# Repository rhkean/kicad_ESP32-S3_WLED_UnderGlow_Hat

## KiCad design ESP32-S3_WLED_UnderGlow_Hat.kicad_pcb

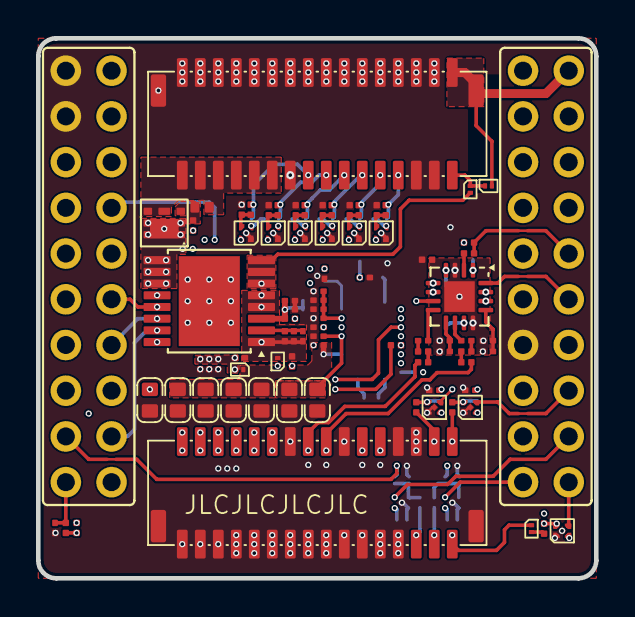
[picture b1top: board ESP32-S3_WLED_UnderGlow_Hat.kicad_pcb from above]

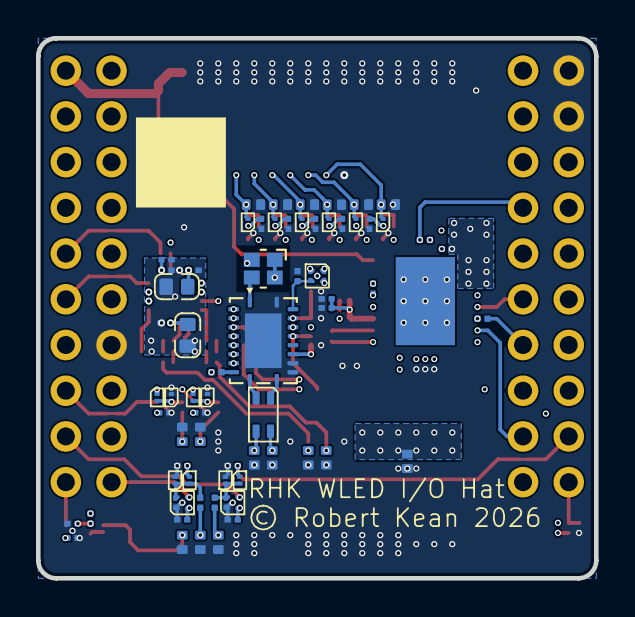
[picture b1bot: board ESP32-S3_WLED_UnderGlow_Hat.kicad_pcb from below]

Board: 6 copper layers, 31.0 x 30.0 mm, 149 parts (66 on the bottom side), 85 nets.

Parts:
C301, C702, C703, C705, C711, C713, C714, C715, C716, C717, C801, C802, C803, C804, C805, C806, C807, C808, C809, C810, C812, C813, C815, C819, C820, C821, C822, C901, C902, C903, C904, C905, C906, C907, C908, C909, C911, C912, C913, C914, C916: 0.1uF; C_0201_Dense
C701, C704, C706, C707, C708, C709, C710, C811, C816: 22uF; C_0603_Dense
C814, C817, C818: 1uF; C_0201_Dense
C910, C915: 4.7nF; C_0201_Dense
CMC701: CMC 0805; CMC_0805
CN301, CN302: SM32B-NSHDZS-1-TF; JST_NSHD_SM32B-NSHD_2x16_P1.0mm_Horizontal_SMD
D701, D801, D803, D804, D806, D807, D809, D810, D812, D813, D901, D902, D903, D904, D908, D909, D912, D913, D914: PMEG4002ESFYL; DFN0603-2
D702, D703, D815, D816: SZESD7241N2T5G; DFN1006-2
D704, D802, D805, D808, D811, D814, D905, D906, D907, D910, D911, D915, D916: D15V0H1U2LP-7B; DFN1006-2
Q901: NTLJS17D0P03P8Z; WDFN6-4_2.05x2.05mm_P0.65mm
R301, R302, R701, R704, R805, R811, R904, R905, R907, R908, R912, R913, R914, R917, R918: 5k1; R_0201_Dense
R702, R807, R808, R809, R810, R812, R901, R902, R903, R906, R910, R911, R915, R916: 33R; R_0201_Dense
R703, R806: 470R; R_0201_Dense
R801, R802, R803, R804: 26k1; R_0201_Dense
R813: 0R; R_0201_Dense
R909: 100k; R_0201_Dense
U301: ESP32-S3_D1_Pico
U701: TCAN4550-Q1; Texas_RGY_R-PVQFN-N20_EP2.05x3.05mm
U702, U801, U802, U803, U804, U805, U901, U902, U904, U905, U906, U907: 74LV1T125; X2SON5_SOT1226_0.8x0.8mm
U806: ES7241D; QFN-16-1EP_3x3mm_P0.5mm_EP1.7x1.7mm
U903: TPS2HCS10A-Q1; Texas_HTSSOP-16-1EP_5.0x4.4mm_P0.65mm_EP5.0x3.4mm_Mask3.313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
Y701: 40MHz; Oscillator_SMD_Abracon_ASAAIG-4Pin_2.0x1.6mm

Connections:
+3V3: C701.1, C702.1, C711.1, C717.1, C801.1, C802.1, C803.1, C804.1, C805.1, C811.1, C812.1, C813.1, C814.1, C815.1, C816.1, R301.2, R701.2, R811.2, R901.1, U301.8 (+3V3_{out}), U301.18 (+3V3), U701.17 (V_{IO}), U702.2 (A), U702.5 (VCC), U801.5 (VCC), U802.5 (VCC), U803.5 (VCC), U804.5 (VCC), U805.5 (VCC), U806.1 (V_{DD}P), U806.4 (V_{DD}D), U806.11 (V_{DD}A), U806.14 (M1), U806.15 (M0), Y701.1 (EN), Y701.4 (Vdd)
+5V_{FUSED}: C806.1, C807.1, C808.1, C809.1, C901.1, C902.1, C903.1, C904.1, C905.1, D801.1 (K), D804.1 (K), D807.1 (K), D810.1 (K), D902.1 (K), D903.1 (K), D908.1 (K), D909.1 (K), D913.1 (K), D914.1 (K), R805.2, U301.9 (+5V_{FUSED_{out}}), U901.5 (VCC), U902.5 (VCC), U904.5 (VCC), U905.5 (VCC), U906.5 (VCC), U907.5 (VCC)
+V_{BAT}: C907.1, C908.1, C909.1, C910.1, CN302.1, CN302.3, CN302.5, CN302.7, CN302.9, CN302.11, D701.2 (A), D704.1 (K), U903.EP (V_{BB})
+V_{SW}: CN301.21, CN301.23, CN301.25 (Pin_23), CN301.27 (Pin_23), CN301.29 (Pin_23), CN301.31 (Pin_23), D907.1 (K), Q901.3 (S), Q901.4 (S)
/IO_Board/AUX_{L}: CN302.15, D815.1 (A1), R807.2
/IO_Board/AUX_{R}: CN302.17, D816.1 (A1), R810.2
/IO_Board/Brake: U301.39 (IO16), U802.4 (Y)
/IO_Board/Brake_{IN}: CN302.28 (Pin_24), D805.1 (K), R802.2
/IO_Board/CAN Bus/+V_{SUP}: C705.1, C707.1, C708.1, C709.1, C710.1, D701.1 (K), U701.14 (V_{SUP})
/IO_Board/CAN Bus/CAN_F_N: CMC701.2, U701.10 (CANL)
/IO_Board/CAN Bus/CAN_F_P: CMC701.1, U701.11 (CANH)
/IO_Board/CAN Bus/FLTR: C713.1, C714.1, C715.1, C716.1, U701.18 (FLTR)
/IO_Board/CAN Bus/GPO2: R703.2, U701.9 (GPO2)
/IO_Board/CAN Bus/OSC1: U701.1 (OSC1), Y701.3 (OUT)
/IO_Board/CAN Bus/RST: R704.2, U701.19 (RST), U702.4 (Y)
/IO_Board/CAN Bus/SDO: R702.1, U701.6 (SDO)
/IO_Board/CAN Bus/V_{CC_{OUT}}: C703.1, C704.1, C706.1, U701.16 (V_{CCOUT})
/IO_Board/CAN_N: CMC701.3, CN302.23, D702.1 (A1)
/IO_Board/CAN_P: CMC701.4, CN302.21, D703.1 (A1)
/IO_Board/Data1: CN301.17, D902.2 (A), D905.1 (K), R902.1
/IO_Board/Data2: CN301.15, D903.2 (A), D906.1 (K), R903.1
/IO_Board/Data3: CN301.13, D908.2 (A), D910.1 (K), R910.1
/IO_Board/Data4: CN301.11, D909.2 (A), D911.1 (K), R911.1
/IO_Board/Data5: CN301.9, D913.2 (A), D915.1 (K), R915.1
/IO_Board/Data6: CN301.7, D914.2 (A), D916.1 (K), R916.1
/IO_Board/FSPI_{CLK}: U301.6 (FSPI_{CLK}), U701.4 (SCLK), U903.16 (SCLK)
/IO_Board/FSPI_{MISO}: R702.2, R906.2, U301.17 (FSPI_{MISO})
/IO_Board/FSPI_{MOSI}: U301.16 (FSPI_{MOSI}), U701.5 (SDI), U903.13 (SDI)
/IO_Board/GR86 Inputs/A_{IN}L: C817.2, U806.8 (A_{IN}L)
/IO_Board/GR86 Inputs/A_{IN}R: C818.2, U806.10 (A_{IN}R)
/IO_Board/GR86 Inputs/Brake_F: D804.2 (A), D806.1 (K), R802.1, U802.2 (A)
/IO_Board/GR86 Inputs/GND3: C811.2, C812.2, C813.2, C814.2, C815.2, C816.2, C819.2, C820.2, C821.2, C822.2, R813.1, U806.3 (GND_{D}), U806.12 (GND_{A}), U806.17 (GND_{P})
/IO_Board/GR86 Inputs/LTurn_F: D810.2 (A), D812.1 (K), R804.1, U804.2 (A)
/IO_Board/GR86 Inputs/RC_{808-817}: C817.1, R808.1
/IO_Board/GR86 Inputs/RC_{809-818}: C818.1, R809.1
/IO_Board/GR86 Inputs/REF_{P}: C819.1, C820.1, U806.13 (REF_{P})
/IO_Board/GR86 Inputs/REF_{Q}: C821.1, C822.1, U806.9 (REF_{Q})
/IO_Board/GR86 Inputs/RR_{807-808}: R807.1, R808.2
/IO_Board/GR86 Inputs/RR_{809-810}: R809.2, R810.1
/IO_Board/GR86 Inputs/RTurn_F: D807.2 (A), D809.1 (K), R803.1, U803.2 (A)
/IO_Board/GR86 Inputs/Rev_F: D801.2 (A), D803.1 (K), R801.1, U801.2 (A)
/IO_Board/GR86 Inputs/SD_{OUT}: R812.2, U806.2 (SD_{OUT})
/IO_Board/GR86 Inputs/~Dome_F: C810.1, R805.1, R806.2, U805.2 (A)
/IO_Board/I^{2}S_{MCLK}: U301.36 (I^{2}S_{MCLK}), U806.16 (MCLK)
/IO_Board/I^{2}S_{SCK}: U301.26 (I^{2}S_{SCK}), U806.5 (SCLK)
/IO_Board/I^{2}S_{SD}: R811.1, R812.1, U301.35 (I^{2}S_{SD})
/IO_Board/I^{2}S_{WS}: U301.37 (I^{2}S_{WS}), U806.6 (LRCK)
/IO_Board/LED1: U301.32 (IO44), U901.2 (A)
/IO_Board/LED2: U301.23 (IO43), U902.2 (A)
/IO_Board/LED3: U301.33 (IO42), U904.2 (A)
/IO_Board/LED4: U301.24 (IO40), U905.2 (A)
/IO_Board/LED5: U301.34 (IO41), U906.2 (A)
/IO_Board/LED6: U301.25 (IO38), U907.2 (A)
/IO_Board/LTurn: U301.29 (IO17), U804.4 (Y)
/IO_Board/LTurn_{IN}: CN302.29 (Pin_23), D811.1 (K), R804.2
/IO_Board/RLY+: CN301.1, D901.1 (K), D904.1 (K)
/IO_Board/RTurn: U301.38 (IO18), U803.4 (Y)
/IO_Board/RTurn_{IN}: CN302.31 (Pin_23), D808.1 (K), R803.2
/IO_Board/Reverse: U301.30 (IO08), U801.4 (Y)
/IO_Board/Reverse_{IN}: CN302.30 (Pin_24), D802.1 (K), R801.2
/IO_Board/WD: U301.13 (IO02), U701.3 (GPIO1)
/IO_Board/WLED Outputs/LED1_{Buf}: R902.2, R904.1, U901.4 (Y)
/IO_Board/WLED Outputs/LED2_{Buf}: R903.2, R905.1, U902.4 (Y)
/IO_Board/WLED Outputs/LED3_{Buf}: R910.2, R912.1, U904.4 (Y)
/IO_Board/WLED Outputs/LED4_{Buf}: R911.2, R913.1, U905.4 (Y)
/IO_Board/WLED Outputs/LED5_{Buf}: R915.2, R917.1, U906.4 (Y)
/IO_Board/WLED Outputs/LED6_{Buf}: R916.2, R918.1, U907.4 (Y)
/IO_Board/WLED Outputs/SDO: R906.1, U903.14 (SDO)
/IO_Board/WLED Outputs/SNS: C915.1, R907.1, R908.1, U903.2 (SNS)
/IO_Board/WLED Outputs/VDD_{HSS}: C911.1, C912.1, C913.1, C914.1, R901.2, U903.3 (V_{DD})
/IO_Board/WLED Outputs/V_{GATE}: D907.2 (A), Q901.2 (G), R909.2
/IO_Board/WLED Outputs/V_{OUT1}: C906.1, D901.2 (A), U903.6 (V_{OUT1}), U903.7 (V_{OUT1}), U903.8 (V_{OUT1})
/IO_Board/WLED Outputs/V_{OUT2}: C916.1, Q901.1 (D), U903.9 (V_{OUT2}), U903.10 (V_{OUT2}), U903.11 (V_{OUT2})
/IO_Board/~CS_{CAN}: U301.20 (I005), U701.7 (~CS)
/IO_Board/~CS_{HSS}: U301.19 (IO06), U903.15 (~CS)
/IO_Board/~Dome_{IN}: CN302.32 (Pin_24), D813.1 (K), D814.1 (K)
/IO_Board/~Dome: U301.40 (IO15), U805.4 (Y)
/IO_Board/~FLT_{BUS}: R301.1, R302.2, U701.8 (~INT), U903.12 (FLT)
/IO_Board/~FLT_{GBL}: C301.1, R302.1, U301.10 (IO07)
/IO_Board/~Reset Node: R703.1, U301.11 (EN/~RST), U702.1 (OE), U806.7 (~Reset)
/IO_Board/~Wake: R701.1, U301.14 (IO04), U701.2 (~WKRQ)
GND: C301.2, C701.2, C702.2, C703.2, C704.2, C705.2, C706.2, C707.2, C708.2, C709.2, C710.2, C711.2, C713.2, C714.2, C715.2, C716.2, C717.2, C801.2, C802.2, C803.2, C804.2, C805.2, C806.2, C807.2, C808.2, C809.2, C810.2, C901.2, C902.2, C903.2, C904.2, C905.2, C907.2, C908.2, C909.2, C911.2, C912.2, C913.2, C914.2, CN301.3, CN301.4, CN301.5, CN301.6, CN301.8, CN301.10, CN301.12, CN301.14, CN301.16, CN301.18, CN301.19, CN301.20, CN301.22, CN301.24, CN301.26 (Pin_24), CN301.28 (Pin_24), CN301.30 (Pin_24), CN301.32 (Pin_24), CN301.MP2 (MountPin), CN302.2, CN302.4, CN302.6, CN302.8, CN302.10, CN302.12, CN302.13, CN302.14, CN302.16, CN302.18, CN302.19, CN302.20, CN302.22, CN302.24, CN302.25 (Pin_23), CN302.26 (Pin_24), CN302.27 (Pin_23), CN302.MP1 (MountPin), CN302.MP2 (MountPin), D702.2 (A2), D703.2 (A2), D704.2 (A), D802.2 (A), D803.2 (A), D805.2 (A), D806.2 (A), D808.2 (A), D809.2 (A), D811.2 (A), D812.2 (A), D814.2 (A), D815.2 (A2), D816.2 (A2), D905.2 (A), D906.2 (A), D910.2 (A), D911.2 (A), D912.1 (K), D915.2 (A), D916.2 (A), R704.1, R813.2, R904.2, R905.2, R912.2, R913.2, R914.2, R917.2, R918.2, U301.1 (GND), U301.2 (GND), U301.27 (GND), U701.12 (WAKE), U701.13 (GND), U701.20 (OSC2), U701.21 (GND), U702.3 (GND), U801.1 (OE), U801.3 (GND), U802.1 (OE), U802.3 (GND), U803.1 (OE), U803.3 (GND), U804.1 (OE), U804.3 (GND), U805.1 (OE), U805.3 (GND), U901.1 (OE), U901.3 (GND), U902.1 (OE), U902.3 (GND), U904.1 (OE), U904.3 (GND), U905.1 (OE), U905.3 (GND), U906.1 (OE), U906.3 (GND), U907.1 (OE), U907.3 (GND), Y701.2 (GND)
GND0: CN301.2, CN301.MP1 (MountPin), D904.2 (A), U301.31 (GND0)
GND2: C906.2, C910.2, C915.2, C916.2, D912.2 (A), R907.2, R908.2, R909.1, R914.1, U903.1 (GND), U903.4 (DI), U903.5 (LHI)
unnamed: D813.2 (A), R806.1

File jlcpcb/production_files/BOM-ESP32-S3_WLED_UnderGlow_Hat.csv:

Comment,Designator,Footprint,LCSC,Quantity
0.1uF,"C301,C702,C703,C705,C711,C713,C714,C715,C716,C717,C801,C802,C803,C804,C805,C806,C807,C808,C809,C810,C812,C813,C815,C819,C820,C821,C822,C901,C902,C903,C904,C905,C906,C907,C908,C909,C911,C912,C913,C914,C916",C_0201_Dense,C915760,41
0R,R813,R_0201_Dense,C6491732,1
100k,R909,R_0201_Dense,C226394,1
1uF,"C814,C817,C818",C_0201_Dense,C335102,3
22uF,"C701,C704,C706,C707,C708,C709,C710,C811,C816",C_0603_Dense,C29519229,9
26k1,"R801,R802,R803,R804",R_0201_Dense,C910625,4
33R,"R702,R807,R808,R809,R810,R812,R901,R902,R903,R906,R910,R911,R915,R916",R_0201_Dense,C226514,14
4.7nF,"C910,C915",C_0201_Dense,C85933,2
40MHz,Y701,Oscillator_SMD_Abracon_ASAAIG-4Pin_2.0x1.6mm,C1852570,1
470R,"R703,R806",R_0201_Dense,C226558,2
5k1,"R301,R302,R701,R704,R805,R811,R904,R905,R907,R908,R912,R913,R914,R917,R918",R_0201_Dense,C226588,15
74LV1T125,"U702,U801,U802,U803,U804,U805,U901,U902,U904,U905,U906,U907",X2SON5_SOT1226_0.8x0.8mm,C547939,12
CMC 0805,CMC701,CMC_0805,C448605,1
D15V0H1U2LP-7B,"D704,D802,D805,D808,D811,D814,D905,D906,D907,D910,D911,D915,D916",DFN1006-2,C1973850,13
ES7241D,U806,QFN-16-1EP_3x3mm_P0.5mm_EP1.7x1.7mm,C389154,1
NTLJS17D0P03P8Z,Q901,WDFN6-4_2.05x2.05mm_P0.65mm,C604410,1
PMEG4002ESFYL,"D701,D801,D803,D804,D806,D807,D809,D810,D812,D813,D901,D902,D903,D904,D908,D909,D912,D913,D914",DFN0603-2,C22435168,19
SZESD7241N2T5G,"D702,D703,D815,D816",DFN1006-2,C604770,4
TCAN4550-Q1,U701,Texas_RGY_R-PVQFN-N20_EP2.05x3.05mm,C2876736,1
TPS2HCS10A-Q1,U903,Texas_HTSSOP-16-1EP_5.0x4.4mm_P0.65mm_EP5.0x3.4mm_Mask3.313x2.78mm,C22454438,1
SM32B-NSHDZS-1-TF,CN302,JST_NSHD_SM32B-NSHD_2x16_P1.0mm_Horizontal_SMD,,1
SM32B-NSHDZS-1-TF,CN301,JST_NSHD_SM32B-NSHD_2x16_P1.0mm_Horizontal_SMD,,1

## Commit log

2026-05-03 removed SPI_and_GBL_FLT.kicad_sch
2026-05-05 Update .gitignore, CANBus_Interface.kicad_sch, ESP32-S3_WLED_UnderGlow_Hat-2026-05-04_233126.zip, and 17 more files
2026-05-05 replaced Device:C with Device:C_Small and Device:R with Device:R_Small
2026-05-05 Updated Net Names for FSPI and I2S nets
2026-05-05 Update .gitignore, ESP32-S3_WLED_UnderGlow_Hat-2026-05-05_083139.zip, ESP32-S3_WLED_UnderGlow_Hat.kicad_pcb, and 1 more file
2026-05-06 schematic updated with new ESP32-S3_D1_Pico symbol
2026-05-06 updated pcb with new ESP32-S3_D1_Pico footprint
2026-05-06 1mm fillets
2026-05-07 added ESP32-S3 D1 Pico symbol and footprint
2026-05-07 Created new edge cut
2026-06-14 JLCPCB: W2026061412450502 2026-06-14 PCB: Y62-5297522A PCBA: SMT026061460215-5297522A
2026-06-14 Update .gitignore, ESP32-S3_WLED_UnderGlow_Hat-2026-05-04_233126.zip, ESP32-S3_WLED_UnderGlow_Hat-2026-05-04_233720.zip, and 3 more files

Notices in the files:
ESP32-S3_WLED_UnderGlow_Hat.kicad_pcb:
© Robert Kean 2026
